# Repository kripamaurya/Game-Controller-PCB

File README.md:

# 🎮 DIY Game Controller PCB

A custom game controller PCB designed in KiCad 10.

## ✨ Features
- ✅ Joystick support
- ✅ Push buttons
- ✅ Compact PCB layout
- ✅ DIY gaming controller design

## 🛠 Software Used
- KiCad 10

## 📦 Project Files
- Schematic
- PCB Layout
- Custom Footprints

## 📷 Preview

## 🚀 Designed By
TSAR INDUSTRY

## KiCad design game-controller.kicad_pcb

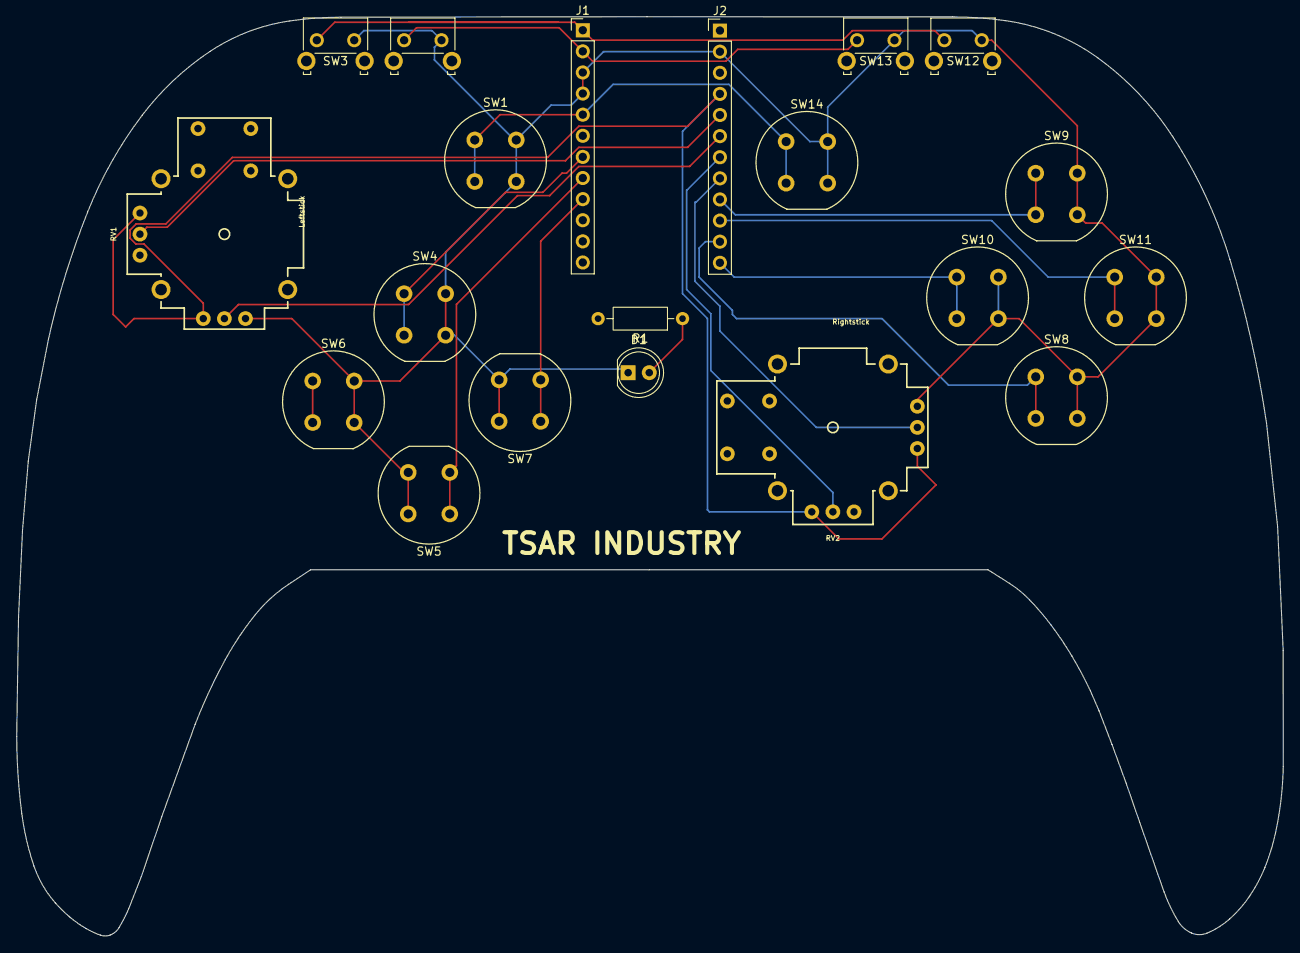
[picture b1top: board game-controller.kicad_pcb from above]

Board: 2 copper layers, 152.4 x 110.6 mm, 20 parts (0 on the bottom side), 18 nets.

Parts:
D1: LED; LED_D5.0mm
J1, J2: Conn_01x12_Pin; PinHeader_1x12_P2.54mm_Vertical
R1: R; R_Axial_DIN0207_L6.3mm_D2.5mm_P10.16mm_Horizontal
RV1: Leftstick; Joystick (1)
RV2: Rightstick; Joystick (1)
SW1, SW14: Backbutton; Push_E-Switch_KS01Q01
SW2: Leftbutton; SW_Tactile_SKHH_Angled
SW3: Lefttrigger; SW_Tactile_SKHH_Angled
SW4: UP; Push_E-Switch_KS01Q01
SW5: DOWN; Push_E-Switch_KS01Q01
SW6: LEFT; Push_E-Switch_KS01Q01
SW7: RIGHT; Push_E-Switch_KS01Q01
SW8: B; Push_E-Switch_KS01Q01
SW9: Y; Push_E-Switch_KS01Q01
SW10: A; Push_E-Switch_KS01Q01
SW11: X; Push_E-Switch_KS01Q01
SW12: Righttrigger; SW_Tactile_SKHH_Angled
SW13: Rightbutton; SW_Tactile_SKHH_Angled

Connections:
/A0: J2.8, RV2.5
/A1: J2.7, RV2.2
/A2: J2.6, RV1.5
/A3: J2.5, RV1.2
/D0: J1.1, SW3.1, SW12.1
/D1: J1.2, SW2.1, SW13.1
/D2: J1.5, SW1.1, SW1.3, SW14.1, SW14.3
/D3: SW6.1, SW6.3
/D4: J1.7, SW4.1, SW4.3
/D5: J1.8, SW5.1, SW5.3
/D6: J1.9, SW7.1, SW7.3
/D10: J2.12, SW10.1, SW10.3
/D14: J2.10, SW11.1, SW11.3
/D15: J2.9, SW9.1, SW9.3
/D16: J2.11, SW8.1, SW8.3
/GND: D1.1 (K), J1.3, J1.4, J2.2, RV1.6, RV2.6, SW1.2, SW1.4, SW2.2, SW3.2, SW4.2, SW4.4, SW5.2, SW5.4, SW6.2, SW6.4, SW7.2, SW7.4, SW8.2, SW8.4, SW9.2, SW9.4, SW10.2, SW10.4, SW11.2, SW11.4, SW12.2, SW13.2, SW14.2, SW14.4
/VCC: J2.4, RV1.1, RV1.4, RV2.1, RV2.4
unnamed: D1.2 (A), R1.1

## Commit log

2026-05-18 Create README.md for DIY Game Controller PCB
    Added initial project documentation for DIY Game Controller PCB.
2026-05-18 Update README with PCB preview images
    Add PCB preview images to the README
